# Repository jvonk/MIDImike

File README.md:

# MIDImike

While playing my clarinet, I realized that it would be fun to hear other instruments, such as a guitar, piano or even a choir ensemble playing alongside me! It would be equally nice to be able to have these melodies transcribed on paper or electronically. All existing solutions to these problems required a bulky computer or a cell phone, whereas creating this compact device would combine my interest for music with my passion for engineering and math to create something useful!

This project allows you to create a small, affordable, and accurate device that listens to a musical instrument and recognizes the notes played. It displays the music on a clef or as piano roll. These notes can then be sent to a synthesizer using the MIDI protocol. This allows musicians to hear other instruments playing alongside with them, and also allows them store their compositions.

A short video of an early prototype

## Clone

We'll start by cloning the repository and its submodules to a local directory. The `--recursive` flag automatically initializes and updates the submodules in the repository.

```bash
git clone --recursive https://github.com/jvonk/Arduino_Pitch-Detector.git
```

or using `ssh`

```bash
git clone --recursive git@github.com:jvonk/Arduino_Pitch-Detector.git
```

## Hardware

This project uses inputs from an amplified microphone and outputs them, after processing, to a TFT display and USB-MIDI connection. To use the optional USB-MIDI output, you will need to replace the firmware on the ATmega16U2 companion chip.

### Schematic

Power

Logic

A few notes:

- When lit, `LED1` indicates that the signal exceeds the maximum level.
- When connected, `JP1` selects the USB-MIDI output. Otherwise, USB-SERIAL is selected. To upload the sketch, this jumper needs to be open, and the Arduino power must be cycled.
- Push button, `SW1` was used during development to replay stored MIDI notes.
- Switch `SW2`, is for a future extension that corrects the pitch for transposing instruments.

> Remember to connect the 3.3 Volt output from the Arduino to the `AREF` input on the Arduino. Without this, no notes will be displayed.

### Board

This is totally overkill, but the `.brd` file can be found the in `hardware` directory.

Note that the footprint of `PCB1` is mirrored, and `MISO2` and `MOSI2` should be connected in rev 1 of the board. These problems are corrected in rev 2.

### Bill of materials

| Name | Description                                        | Suggested mfr and part#   |                                                                                                      Paid |
| ---- | -------------------------------------------------- | ------------------------- | --------------------------------------------------------------------------------------------------------: |
| PCB1 | Electret microphone w/ auto gain control           | Adafruit 1713             |  [$7.95](https://www.adafruit.com/product/1713) |
| PCB2 | Arduino Uno R3 or Arduino METRO 328                | Adafruit 2488             | [$17.50](https://www.adafruit.com/product/2488) |
| PCB3 | ST7735R 1.8" Color TFT display w/ MicroSD breakout | Adafruit 802              | [$19.95](https://www.adafruit.com/product/802) |
| HDR  | Shield stacking headers for Arduino                | Adafruit 85               |  [$1.95](https://www.digikey.com/en/products/detail/adafruit-industries-llc/85/5154649)
| LED1 | LED, Amber Clear 602nm, 1206                       | Lite-On LTST-C150AKT      |  [$0.33](https://www.digikey.com/en/products/detail/lite-on-inc/LTST-C150AKT/269213) |
| R1   | Resistor, 330 Ω, 1/8 W, 0805                       | YAGEO RC0805FR-0768RL     |  [$0.10](https://www.digikey.com/en/products/detail/yageo/RC0805FR-07330RL/727866) |
| JP1  | Connector header, vertical 3 pos, 2.54mm           | Metz Connect PR20203VBNN  |  [$0.10](https://www.digikey.com/en/products/detail/metz-connect-usa-inc/PR20203VBNN/7794768) |
| SW1  | Switch tactile, SPST-NO, 0.05A/24V                 | TE Connectivity 1825910-3 |  [$0.15](https://www.digikey.com/en/products/detail/te-connectivity-alcoswitch-switches/1825910-3/2400476) |
| SW2  | Switch rotary dip BDC comp, 100mA/5V               | Nidec Copal SH-7030TB     |  [$2.00](https://www.digikey.com/en/products/detail/nidec-copal-electronics/SH-7030TB/2057869) |

### Notes

For the microphone, I use the Adafruit microphone breakout, because it has a 1.25 Volt DC bias and includes an automatic gain control. The "max gain" is set to 40 dB by connecting the `GAIN` to `5V`. Other microphones will work for as long as they have a DC biased output, and the output signal is strong enough.

The popular Arduino UNO R3 forms the heart of the system. Note that the REPLAY signal was only used during debugging. This board is now becoming hard to find, so you can also use the Arduino METRO 328 or possibly other boards instead.

If you’re going to reprogram the `Atmega16u2`, you need access the companion chip header (ICSP1) as marked in the illustration below.

## Software

The software on the Arduino transforms the sound wave to an electrical signal, uses autocorrelation to find the frequency played, and then displays the frequency as note onscreen, in addition to outputting it to a MIDI synthesizer.

### Requirements

| Component                          | Version tested       |
| ---------------------------------- | -------------------- |
| Arduino IDE                        | 1.8.19 (&ge; 1.6.12) |
| Arduino AVR Boards                 | 1.8.5 (&ge; 1.6.14)  |
| Bill Greiman SdFat library         | 2.1.2                |
| Adafruit BusIO library             | 1.11.5               |
| Adafruit ST7735 and ST7789 library | 1.9.3                |
| Adafruit GFX Library               | 1.11.0               |

### Build

- Install the libraries.
- If switch `SW1` is closed, open it and power-cycle the device.
- Using the Arduino IDE or Visual Code
  - Specify the board, COM port and baud rate.
  - Build and upload the sketch .

By default the USB port is used for USB-MIDI, so monitoring the serial port will not show anything of use.

The device is now ready to show the pitch of notes played!

If you want to connect it using USB-MIDI, continue reading.

## USB-MIDI

> Instructions below are for / tested on Windows, but should equally apply to Linix and MacOS;

The USB on the Arduino talks USB-SERIAL with the host computer. That is how the Serial.print() statements end up on the serial monitor. A small companion chip (ATmega16U2) on the Arduino acts a UART/USB-serial bridge.

We reprogram this companion chip on the Arduino UNO R3 such that, when `SW1` is closed and you power-cycle the device, it appears as a MIDI peripheral (HID), or alternatively as the usual USB-SERIAL port.

It is important that the Arduino can still behave as USB-SERIAL device, because this is the usual method of uploading new sketches.

### Match the USB IDs

I patched dualMocoLUFA, so that it matches what is reported by Windows Device Manager's detail `hardware Ids`.

```
USB\VID_2341&PID_0043&REV_0001
```

If your device shows different details, read [dualMocoLUFA/PATCHES.md](dualMocoLUFA/PATCHES.md) first.

### Install

To install the modified dualMocoLUFA firmware on the ATmega16U2m:

- Install the [Atmel FLexible In-system Programmer](https://www.microchip.com/en-us/development-tool/flip) (FLIP).

- Put the Arduino Uno R3 in DFU mode by briefly connecting the `RESET2*` to `GND` on the atmega16u2 ICSP1 header. These are the leftmost pins, near the USB connector, as shown above.

- In Windows Device Manager, it should show up as “Atmel USB Devices > ATmega16U2“. If it shows up as "Unknown device", install the driver from `U:\Program Files (x86)\Atmel\Flip 3.4.7\usb\atmel_usb_dfu.inf`.

- Start Atmel FLIP
  - Device » Select » `ATmega16U2`
  - Settings » Communication » `USB`
  - File » Load HEX File » `dualMocoLUFA/LUFA-100807-patched/Projects/dualMoco.hex`

### Connect

At this point you should be able to connect the Arduino to a computer and see MIDI events using e.g. MidiView

If you have a real synthesizer to connect to, you can try that. Otherwise, I suggest installing a software synthesizer such as

- [CoolSoft MIDIMapper and VirtualMIDISynth](https://coolsoft.altervista.org/en/virtualmidisynth) with sound fonts [FluidR3 GM](https://github.com/urish/cinto/blob/master/media/FluidR3%20GM.sf2) and/or [Timbres of Heaven](http://midkar.com/soundfonts/index.html).

There are many [Software MIDI editors and sequencers](https://en.wikipedia.org/wiki/Comparison_of_MIDI_editors_and_sequencers) to choose from. A few that I tried are:

- [MidiEditor](https://www.midieditor.org/), free. Can record. (Press the "Connect Midi In/Out" button.)
- [MuseScore](https://musescore.org/en), free.
- [Anvil Studio](https://www.anvilstudio.com/), freemium. Can record.
- [Cakewalk](http://www.cakewalk.com/)
- [ScoreCloud](https://scorecloud.com/), freemium; requires sign-in.
- [Presonus Notation](https://www.presonus.com/products/notion), commercial

### Demo

Here's a video recording of the Arduino's MIDI output with SoundCloud. The clarinet excerpt is performed by the U.S. Army Field Band.

## Configuration options

The file `config.h` is used to configure the device.

### SRC

| SRC        | Description                                  |
| ---------- | -------------------------------------------- |
| `SRC_MIC`  | Uses the sound from the attached microphone. |
| `SRC_FILE` | Reads the sound from files on SD card.       |

### DST

| DST             | Description                                                                                                                                    |
| --------------- | ---------------------------------------------------------------------------------------------------------------------------------------------- |
| `DST_STAFF`     | Displays the output of the frequency and pitch detection module on a scrolling G-clef staff.                                                   |
| `DST_PIANOROLL` | Will show the notes and durations on a piano roll.                                                                                             |
| `DST_TEXT`      | Displays the output of the frequency and pitch detection module in a table format on the serial monitor, which can be useful for verification. |

### USB

Configures the USB protocol used. After changing to USB-MIDI, connect MISO2 to GND and power cycle the Arduino board

| SRC          | Description                                                                                                                           |
| ------------ | ------------------------------------------------------------------------------------------------------------------------------------- |
| `USB_MIDI`   | Transmits note events using the USB-MIDI protocol at 31250 baud. Requires `DST_PIANOROLL` so the note segmentation algorighm can run. |
| `USB_SERIAL` | Transmits text using the usual USB-SERIAL protocol at 115200.                                                                         |

## Verification

The testing methodology reflects the three design criteria.

- To test the frequency and pitch detection, I used monophonic samples.
- For note level segmentation, I used commercial solo clarinet recordings.
- To measure the delay between the note being played and it being recognized, I edited the code, adding a timer to measure the delay between audio input and MIDI output.

Instead of taking input from the microphone, the audio samples are read from files on a micro-SD card. The module sddir.cpp expects top level directories `notes` and `solos`. The next level of directories should have the name of the sample rate (e.g. 9615). From there it will recurse the subdirectories and open each `.wav` file.

The pitch detection and note level segmentation algorithms can be tested independently.

### Pitch

To test the frequency and pitch detection, I used clarinet and monophonic piano samples from the University of [Iowa Electronic Music Studios](https://theremin.music.uiowa.edu/index.html). The measured frequencies were written to the serial monitor, and imported into a spreadsheet for evaluation.

#### B♭ Clarinet

#### Piano

#### B♭ Trumpet

#### E♭ Alto Saxophone

### Note level segmentation

The algorithm is considered correct, when it tracks the pitch correctly and the melody of the original file has not been modified.

I used various solo clarinet recordings:

- Ernesto Molinari, Charme (pour clarinette)
- Sean Osborn, A Set for Clarinet Allegro
- Sean Osborn, A Set for Clarinet Adagio
- Traditions of Excellence, book 1, page 38, exercise 4 on DVD

Another choice could have been:

- Monophonic music segmentation dataset (CMMSD) [^1]
  A new data set with annotations for monophonic audio excerpts. Annotations for note (steady state, sustain), transition (transient, release), and rest (silence, noise, reverberation). The data set consists of 36 items, excerpts of commercial recordings of solo performances of classical music. It covers the instruments bass, bassoon, cello, flute, horn, oboe, trombone, trumpet, and violin, and spans several periods of time in history.

[^1]: Henrik von Coler (Technische Universität Berlin) and Alexander Lerch (Georgia Institute of Technology), January 2014, [Proceedings of the AES 53rd International Conference on Semantic Audio](https://www.researchgate.net/publication/260000033_CMMSD_A_Data_Set_for_Note-Level_Segmentation_of_Monophonic_Music)

To verify, I compared the generated MIDI piano roll to the original score, and the synthesized MIDI events to the original performance.

## Design document

More information on the design and implementation can be found [here](https://coertvonk.com/category/sw/arduino/pitch-detector).

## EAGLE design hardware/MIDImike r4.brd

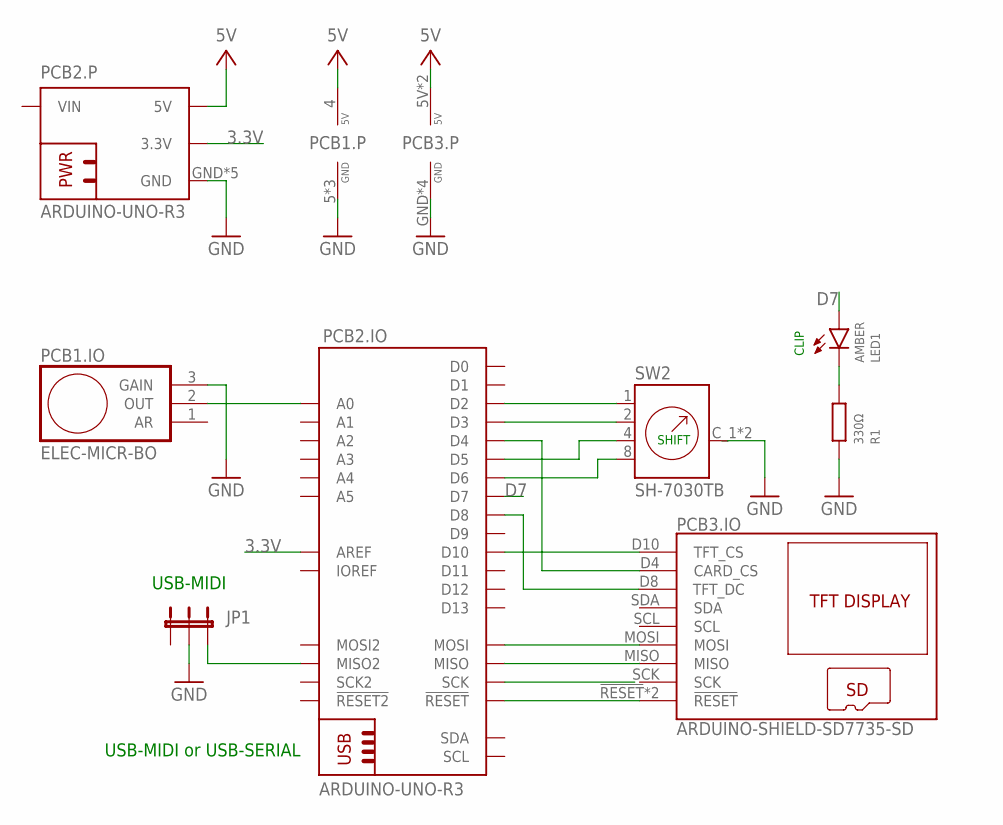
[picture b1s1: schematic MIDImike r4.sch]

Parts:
JP1: JP2E; JP2
LED1: AMBER; CHIPLED_0805
PCB1: ELEC-MICR-BO; ELEC_MICR_BREAKOUT
PCB2: ARDUINO-UNO-R3; ARDUINO-UNO--R3
PCB3: ARDUINO-SHIELD-SD7735-SD; ARDIONO-SHIELD
R1: 330Ω; R0805; MOUSER# 652-CRM0805JW1R5ELF
SW2: SH-7030TB; SW_RDS-16S-1045-SMT-TR

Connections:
3.3V: PCB2.3.3V, PCB2.AREF
5V: PCB1.4 (5V), PCB2.5V, PCB2.5V@1 (5V), PCB2.5V@2 (5V), PCB3.5V, PCB3.5V@1 (5V)
A0: PCB1.2 (OUT), PCB2.A0
D7: LED1.A, PCB2.D7
GND: JP1.2, PCB1.3 (GAIN), PCB1.5 (GND), PCB1.P$1 (GND), PCB1.P$2 (GND), PCB2.GND, PCB2.GND@1 (GND), PCB2.GND@2 (GND), PCB2.GND@3 (GND), PCB2.GND@4 (GND), PCB3.GND, PCB3.GND@1 (GND), PCB3.GND@2 (GND), PCB3.GND@3 (GND), R1.1, SW2.C_1 (C), SW2.C_2 (C)
unnamed: PCB2.D2, SW2.1
unnamed: PCB2.MOSI, PCB3.MOSI
unnamed: JP1.3, PCB2.MISO2
unnamed: PCB2.D10, PCB3.D10 (TFT_CS)
unnamed: PCB2.MISO, PCB3.MISO
unnamed: PCB2.!RESET!, PCB2.!RESET!@1 (!RESET!), PCB3.!RESET!, PCB3.!RESET!@1 (!RESET!)
unnamed: LED1.C, R1.2
unnamed: PCB2.D4, PCB3.D4 (CARD_CS)
unnamed: PCB2.D3, SW2.2
unnamed: PCB2.D8, PCB3.D8 (TFT_DC)
unnamed: PCB2.D5, SW2.4
unnamed: PCB2.D6, SW2.8

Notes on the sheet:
USB-MIDI
USB-MIDI or USB-SERIAL
CLIP
SHIFT

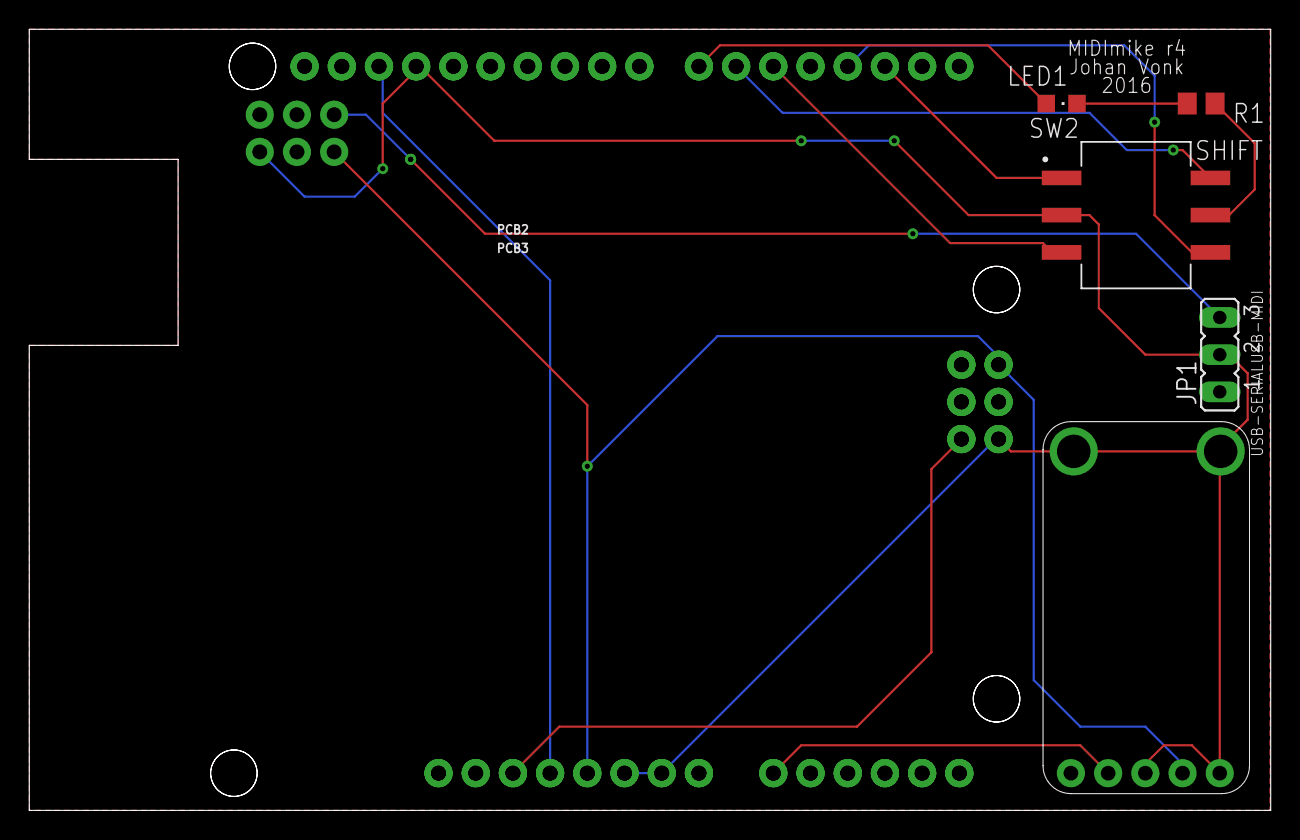
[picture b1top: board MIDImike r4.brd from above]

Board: 2 copper layers, 84.8 x 53.3 mm, 7 parts (0 on the bottom side), 17 nets.

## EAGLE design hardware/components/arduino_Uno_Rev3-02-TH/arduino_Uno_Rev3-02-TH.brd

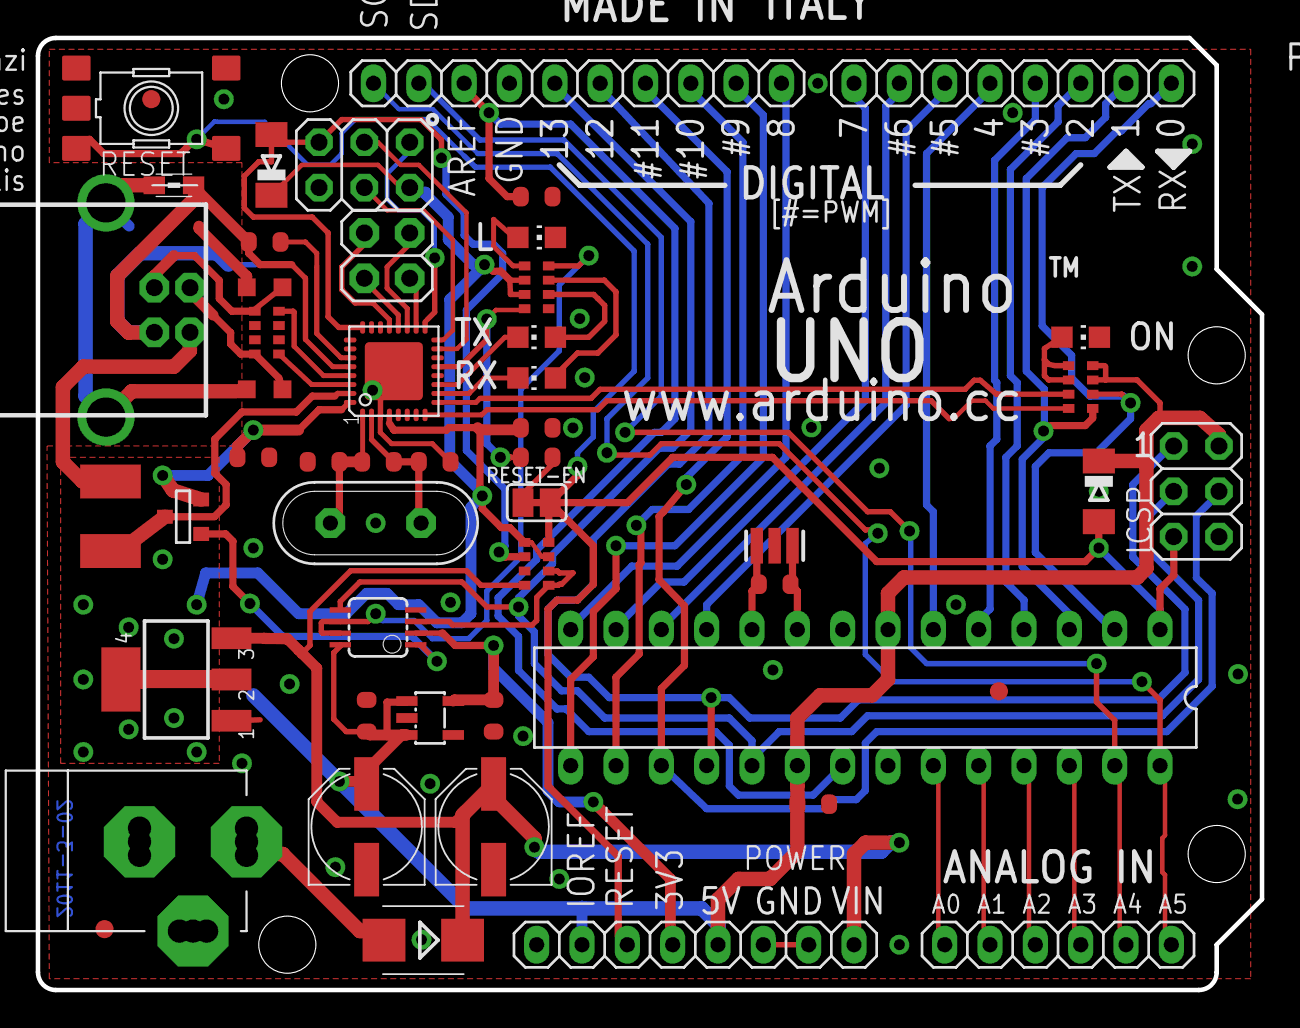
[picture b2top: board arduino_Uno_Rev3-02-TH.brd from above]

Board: 2 copper layers, 68.6 x 53.3 mm, 53 parts (1 on the bottom side), 60 nets.

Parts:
AD: 6x1F-H8.5; 1X06
C1, C2, C4, C5, C6, C7: 100n; C0603-ROUND
C3, C8: 1u; C0603-ROUND
C9, C11: 22p; C0603-ROUND
D1: M7; SMB
D2, D3: CD1206-S01575; MINIMELF
F1: MF-MSMF050-2 500mA; L1812
FD1, FD2, FD3: FIDUCIALMOUNT; FIDUCIA-MOUNT
GROUND: SJ
ICSP, ICSP1: 3x2 M; 2X03
IOH: 10x1F-H8.5; 1X10
IOL: 8x1F-H8.5; 1X08
JP2: 2x2 M - NM; 2X02
L: YELLOW; CHIP-LED0805
L1: BLM21; 0805
ON: GREEN; CHIP-LED0805
PC1, PC2: 47u; PANASONIC_D
POWER: 8x1F-H8.5; 1X08
R1, R2: 1M; R0603-ROUND
RESET: TS42031-160R-TR-7260; TS42
RESET-EN: SJ
RN1: 10K; CAY16
RN2, RN4: 1K; CAY16
RN3: 22R; CAY16
RX: YELLOW; CHIP-LED0805
T1: FDN340P; SOT-23
TX: YELLOW; CHIP-LED0805
U1: NCP1117ST50T3G; SOT223
U2: LP2985-33DBVR; SOT23-DBV
U3: ATMEGA16U2-MU(R); MLF32
U5: LMV358IDGKR; MSOP08
U$1: DISCLAIMER
X1: POWERSUPPLY_DC21MMX; POWERSUPPLY_DC-21MM
X2: USB-B_TH; PN61729
Y1: 16MHz; QS
Y2: CSTCE16M0V53-R0 16MHZ; RESONATOR
Z1, Z2: CG0603MLC-05E; CT/CN0603
ZU4: ATMEGA328P-PU; DIL28-3

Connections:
+3V3: C3.2, POWER.4, U2.5, U5.2
+5V: C1.2, C2.2, C6.2, C7.1, D2.C, D3.C, ICSP.2, ICSP1.2, PC2.+, POWER.2, POWER.5, RN1.3, RN1.5, RN2.2, RN2.3, RN4.3, RN4.4, T1.2, U1.2, U1.4, U2.1, U2.3, U3.4, U3.32, U5.8, ZU4.7, ZU4.20
AD0: AD.1, ZU4.23
AD1: AD.2, ZU4.24
AD2: AD.3, ZU4.25
AD3: AD.4, ZU4.26
AD4/SDA: AD.5, IOH.9, ZU4.27
AD5/SCL: AD.6, IOH.10, ZU4.28
AREF: C4.2, IOH.8, ZU4.21
CMP: RN1.1, RN1.2, U5.3
D+: RN3.5, X2.3, Z1.1
D-: RN3.8, X2.2, Z2.1
DTR: C5.1, RN2.4, U3.13
GATE_CMD: T1.3, U5.1
GND: C1.1, C2.1, C3.1, C4.1, C6.1, C7.2, C9.2, C11.2, GROUND.1, ICSP.6, ICSP1.6, IOH.7, L.C, ON.C, PC1.-, PC2.-, POWER.6, POWER.7, RESET.1, RESET.2, RN1.7, RN2.5, U1.1, U2.2, U3.3, U3.33, U5.4, X1.1, X1.3, Y2.2, ZU4.8, ZU4.22
IO0: IOL.1, RN4.2, ZU4.2
IO1: IOL.2, RN4.1, ZU4.3
IO2: IOL.3, ZU4.4
IO3: IOL.4, ZU4.5
IO4: IOL.5, ZU4.6
IO5: IOL.6, ZU4.11
IO6: IOL.7, ZU4.12
IO7: IOL.8, ZU4.13
IO8: IOH.1, ZU4.14
IO9: IOH.2, ZU4.15
L13: RN2.8, U5.6, U5.7
M8RXD: RN4.7, U3.9
M8TXD: RN4.8, U3.8
MISO: ICSP.1, IOH.5, ZU4.18
MISO2: ICSP1.1, U3.17
MOSI: ICSP.4, IOH.4, ZU4.17
MOSI2: ICSP1.4, U3.16
unnamed: L.A, RN2.1
unnamed: ON.A, RN4.5, RN4.6
unnamed: RN2.7, RX.A
unnamed: RN2.6, TX.A
PB4: JP2.1, U3.18
PB5: JP2.3, U3.19
PB6: JP2.2, U3.20
PB7: JP2.4, U3.21
PWRIN: D1.A, X1.2
RD+: RN3.4, U3.29
RD-: RN3.1, U3.30
RESET: C5.2, D2.A, ICSP.5, POWER.3, RESET.3, RESET.4, RESET-EN.1, RESET-EN.2, RN1.4, ZU4.1
RESET2: D3.A, ICSP1.5, RN1.6, U3.24
RXLED: RX.C, U3.10
SCK: ICSP.3, IOH.6, U5.5, ZU4.19
SCK2: ICSP1.3, U3.15
SS: IOH.3, ZU4.16
TP_VUCAP: C8.1, U3.27
TXLED: TX.C, U3.11
UGND: C8.2, GROUND.2, L1.1, U3.28, X2.4
USBVCC: F1.1, T1.1, U3.31
USHIELD: L1.2, X2.P$1, X2.P$2, Z1.2, Z2.2
VIN: D1.C, PC1.+, POWER.8, RN1.8, U1.3
XT1: C9.1, R1.1, U3.1, Y1.2
XT2: C11.1, R1.2, U3.2, Y1.1
XTAL1: R2.1, Y2.3, ZU4.9
XTAL2: R2.2, Y2.1, ZU4.10
XUSB: F1.2, X2.1

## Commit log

2016-10-12 Add graphic and expand README
2016-10-21 add autobuild cfg, update comments
2016-10-21 Update build image
2016-10-21 Add lib to auto build
2016-10-21 correct typo
2016-10-21 Correct typo ';'
2020-04-14 Created using Colaboratory
2022-04-18 rm files from other prj
2022-05-04 rm const from fnc; sample_t from char to int8_t
2022-05-04 rm unneeded code
2022-05-04 don't wait for serial port connected before start
2022-05-04 update READNE and add schematics
2022-05-04 add youtube video demo
2022-05-04 embed video instead of link
2022-05-04 embed yt video
2022-05-04 embed video
2022-05-06 Update README; add dualMocoLUFA; redo schematic
2022-05-06 add hardware component submodules
2022-05-06 add svg version of schematics for easy viewing
2022-05-06 archive arduino uno r3 schematic and board files
2022-05-06 add newer version of EAGLE eagle2svg utl
2022-05-06 add --recursive instruction
2022-05-06 fix -Wignored-qualifiers
2022-05-06 ouput must be pianoroll for USB-MIDI
2022-05-07 Update synthesizer
2022-05-07 compact
2022-05-07 rm const from fnc return type
2022-05-07 init private struct
2022-05-07 add cakewalk
2022-05-07 add demo video
2022-05-07 add libraries
2022-05-07 mv src in dirs
2022-05-07 rm unneeded
2022-05-07 shrink debug.cpp
2022-05-07 rm bunch of cpp namespaces
2022-05-08 rm C++ fluff
2022-05-08 rm c++ namespaces
2022-05-08 spring cleaning
2022-05-09 spring clean
2022-05-10 fix low notes; clean up
2022-05-10 enable interpolation
2022-05-10 add rotary dip switch to allow for pitch shift
2022-05-11 add sample files; spring cleaning cont'd
2022-05-11 update pcb picts
2022-05-11 update BOM
2022-05-11 switch .wav file reading from SD to SdFat library
2022-05-13 fix autocorrelation threshold not working
2022-05-13 change bridge name to MIDImike
2022-05-14 Fix README.md Grammar and Spelling
    Basic grammar changes & spelling tweaks; improve readability & more
2022-05-22 fix microphone footprint mirrored
2022-05-23 fix MISO input
2022-05-23 fix so that USB-MIDI connects to MISO2
2022-05-23 add/update
2022-05-23 update pcb images
2022-05-23 correct MISO2 (was MOSI2)
2022-05-26 reduce footprint SW2
2022-05-27 fix replay button pin; introduce shift bcd inputs
2022-05-28 rm replay btn; mv clip led to D7
